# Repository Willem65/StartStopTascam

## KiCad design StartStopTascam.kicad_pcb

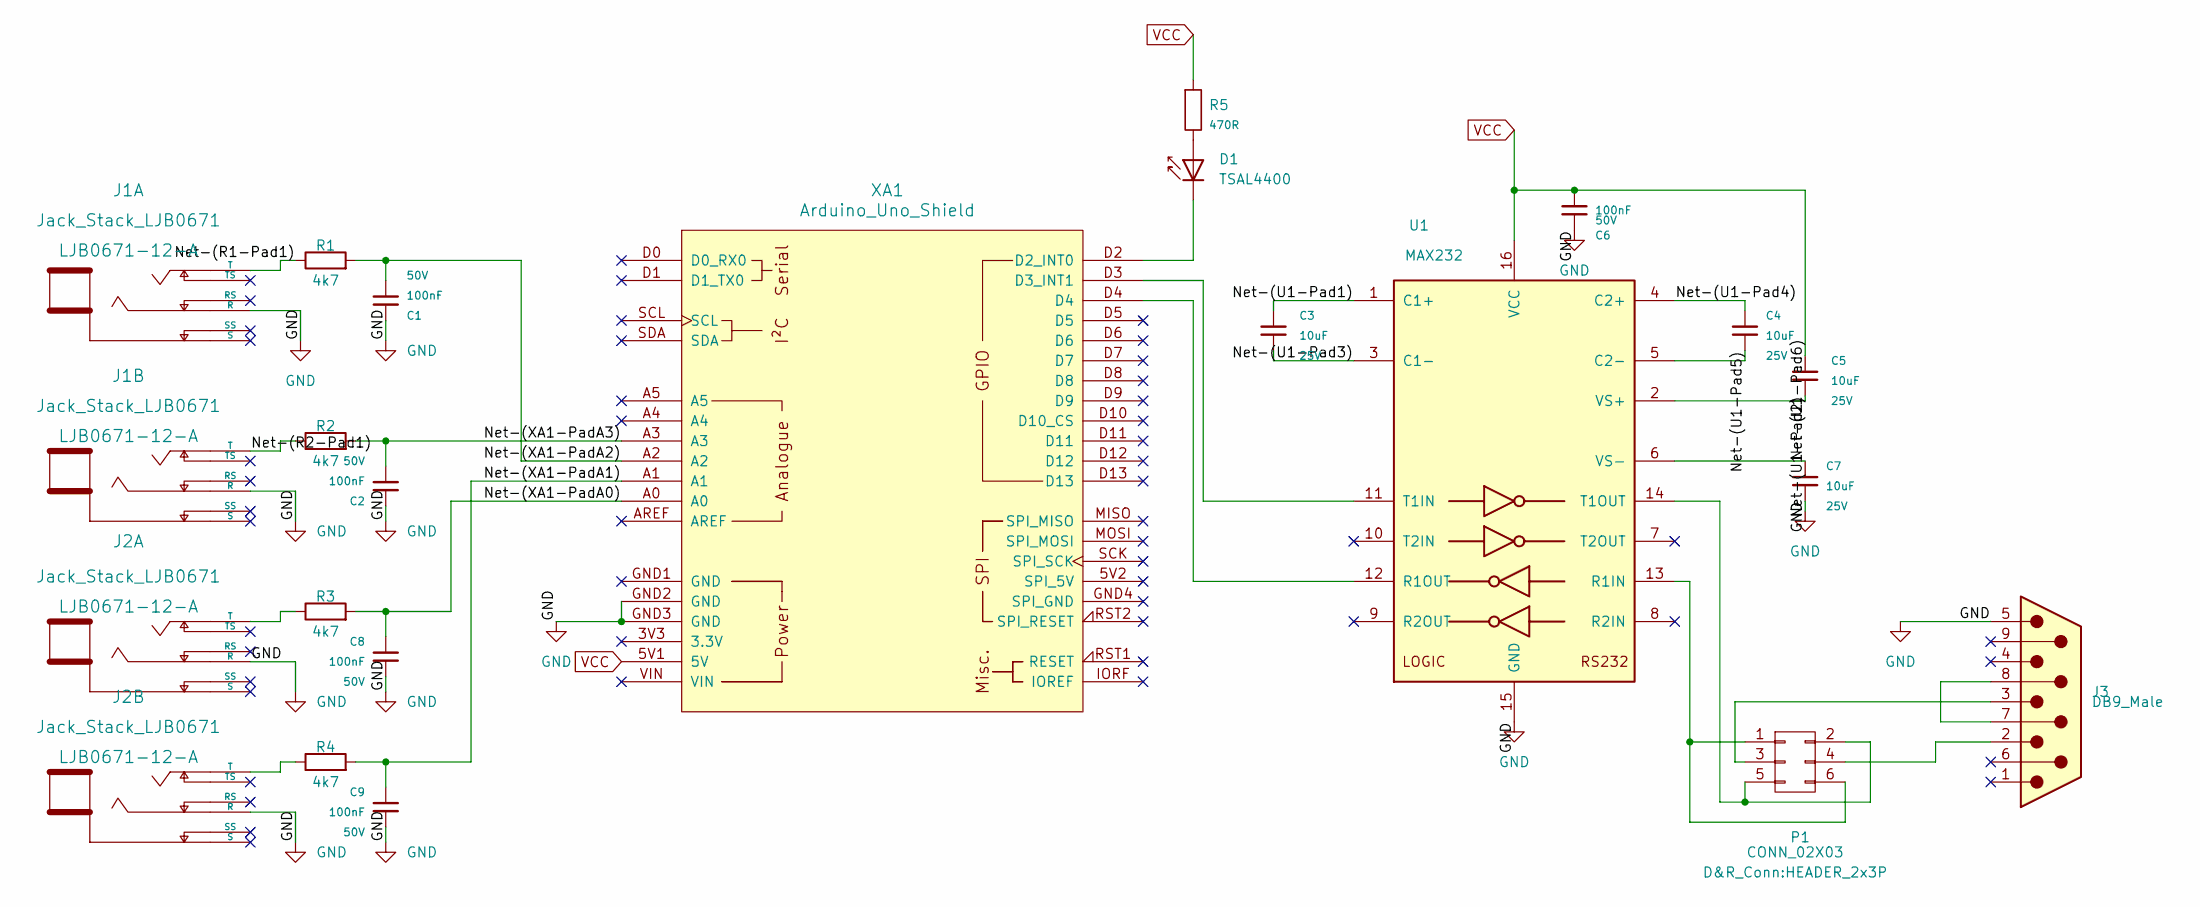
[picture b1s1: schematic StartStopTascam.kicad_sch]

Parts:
C1, C2, C8, C9: 100N-X7R_50V#0603-D&R_Passive; C_0603; Voltage 50V
C3, C4, C5, C7: 10U-X5R_25V#1210; C_1210; Voltage 25V; LCSC C39232
C6: 100N-X7R_50V#0603; C_0603; Voltage 50V
D1: TSAL4400; LED_D3.0mm_IRBlack
J1, J2: Jack_Stack_LJB0671; LJB0671-12
J3: DB9_Male; DSUB-9_Male_Horizontal_P2.77x2.84mm_EdgePinOffset4.94mm_Hou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
P1: CONN_02X03; HEADER_2x3P
R1, R2, R3, R4: 4k7; C_0603
R5: 470R#0603; R_0603; LCSC C23179
U1: MAX232; DIP-16_W7.62mm
XA1: Arduino_Uno_Shield; Arduino_Uno_Shield_Hat

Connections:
/GND: C1.1, C2.1, C6.2, C7.2, C8.1, C9.1, J1.5 (R), J1.7 (R), J2.5 (R), J2.7 (R), J3.5, U1.15 (GND), XA1.GND2 (GND), XA1.GND3 (GND)
/Net-(R1-Pad1): J1.3 (T), R1.1
/Net-(R2-Pad1): J1.1 (T), R2.1
/Net-(U1-Pad1): C3.1, U1.1 (C1+)
/Net-(U1-Pad2): C5.2, U1.2 (VS+)
/Net-(U1-Pad3): C3.2, U1.3 (C1-)
/Net-(U1-Pad4): C4.1, U1.4 (C2+)
/Net-(U1-Pad5): C4.2, U1.5 (C2-)
/Net-(U1-Pad6): C7.1, U1.6 (VS-)
/Net-(XA1-PadA0): C8.2, R3.2, XA1.A0
/Net-(XA1-PadA1): C9.2, R4.2, XA1.A1
/Net-(XA1-PadA2): C1.2, R1.2, XA1.A2
/Net-(XA1-PadA3): C2.2, R2.2, XA1.A3
unnamed: D1.2 (A), R5.2
unnamed: J2.1 (T), R4.1
unnamed: J2.3 (T), R3.1
unnamed: J3.2, P1.4
unnamed: J3.3, P1.3
unnamed: J3.7, J3.8
unnamed: P1.1, P1.6, U1.13 (R1IN)
unnamed: P1.2, P1.5, U1.14 (T1OUT)
unnamed: U1.11 (T1IN), XA1.D3 (D3_INT1)
unnamed: U1.12 (R1OUT), XA1.D4
unnamed: D1.1 (K), XA1.D2 (D2_INT0)
VCC: C5.1, C6.1, R5.1, U1.16 (VCC), XA1.5V1 (5V)

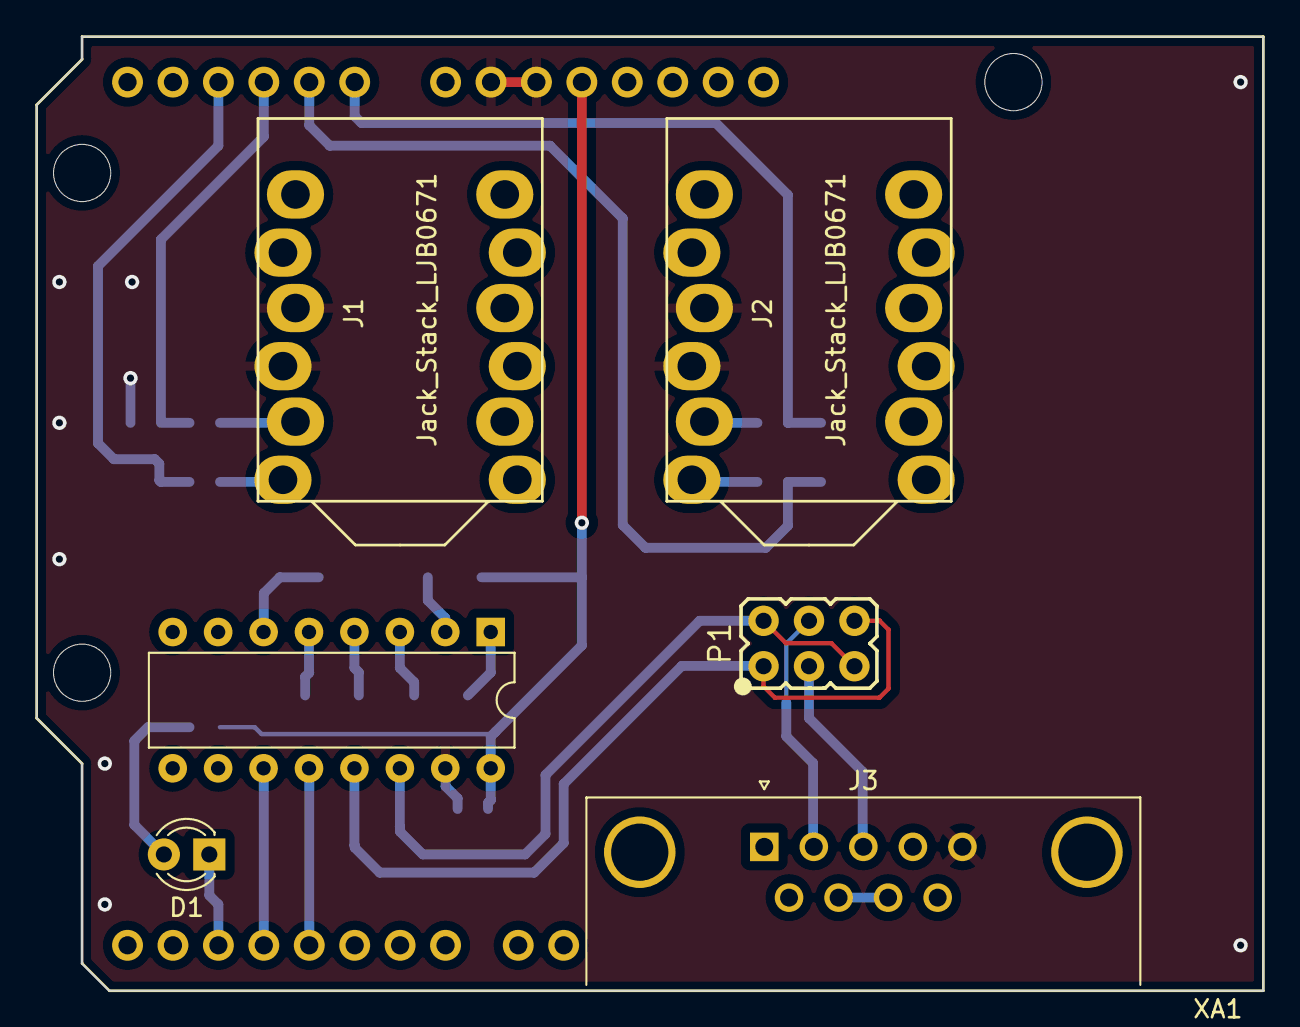
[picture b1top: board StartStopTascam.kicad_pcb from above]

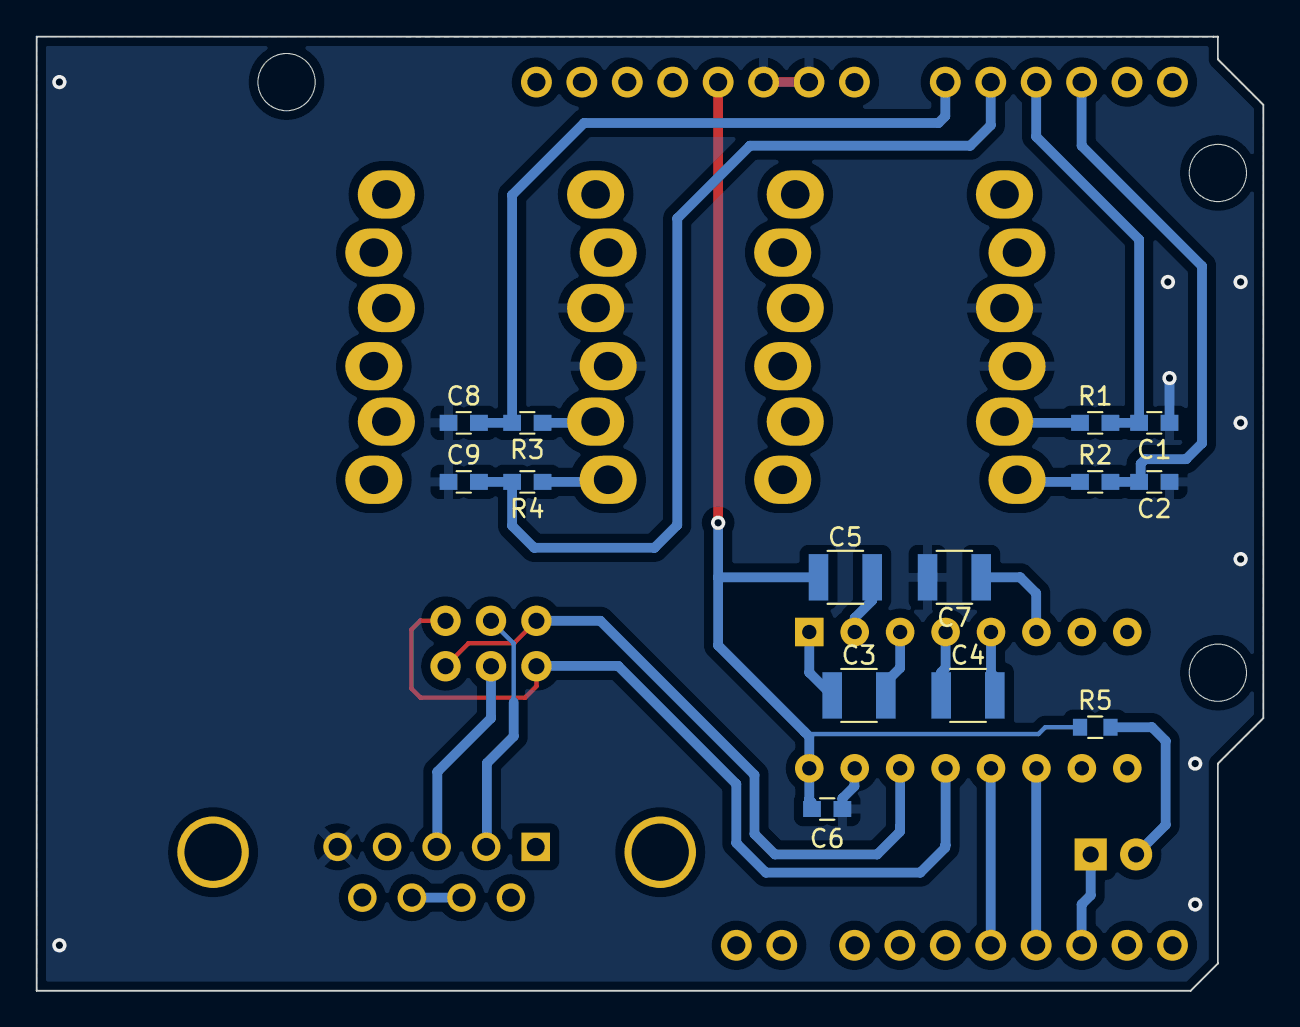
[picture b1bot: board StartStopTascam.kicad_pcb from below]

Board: 2 copper layers, 68.6 x 53.3 mm, 21 parts (14 on the bottom side), 25 nets.

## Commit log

2022-04-18 18042022
2022-04-18 Create StartStopTascam.zip
    kicad
2022-04-20 kicad
2022-05-01 Kicad
    Kicad
2022-05-12 Arduino Uno
    Arduino Uno
2022-10-31 a
    a
